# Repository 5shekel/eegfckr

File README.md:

# eegfckr
TLDR>>> brain exciter, a  sencessor to output blinking LEDs in freq between 4-32Hz and tone in a ~30Hz phase

[text is work in progress, not touching audio]
After centuries of using electricity to stimulate and research the brain, optogenetics marks a phase, in which we use light to activate neurons and their pathways. To understand this transformation from electricity to light as a medium for exploring our mind, we will prototype a creative eye-ware with LEDs, which can alter EEG signals in the brain. We will solder a simple circuit that acts as a mind machine device. The final prototype will have a form of a creative eyewear or "eye-ware" mocking some recent history of Google glass mania and other futuristic attempts to hack eyeglasses.

[more pics at imgur](http://imgur.com/a/cNCWE)

# board Layout  
where abusing attiny85 "factory calibrated" 10% error to generate [binaural beats](https://en.wikipedia.org/wiki/Binaural_beats)   

Attiny85 pinout  

## software
in process.   
also see [low.li blog post](http://low.li/story/2011/01/arduino-brain-machine) > [github](https://github.com/LaughterOnWater/Arduino-Brain-Machine)

### tone talk
links on tone lib modfing for the attiny family and some light low level code talk.
[A Tone Generator for Trinket](http://w8bh.net/avr/TrinketTone.pdf)  
[Waveform Generation using an ATtiny85](http://www.technoblogy.com/show?QVN) | [archive.is](https://archive.is/Lsk9m)  
[tinyTune func](http://www.technoblogy.com/show?KVO)   
[programming the LilyPad Arduino: sound](http://web.media.mit.edu/~leah/LilyPad/07_sound.html)  
[link-an-led-with-an-avr](http://www.evilmadscientist.com/2012/blink-an-led-with-an-avr/)  
[http://www.ladyada.net/learn/proj1/blinky.html](http://www.ladyada.net/learn/proj1/blinky.html)  
[binaureal beats using the arduino](http://forum.arduino.cc/index.php?topic=41077.0)  
[brainwave-disruptor](http://blog.ponoko.com/2011/08/05/rich-decibels-brainwave-disruptor/) >> [polytones without delay](https://gist.github.com/5shekel/ce690d048fac5872f0ad)

### upload
using arduino uno as isp  
- add ATtiny board to arduino 1.6.5> 
(see http://highlowtech.org/?p=1695)  
--(TLDR) add [this](https://raw.githubusercontent.com/damellis/attiny/ide-1.6.x-boards-manager/package_damellis_attiny_index.json) to your board manager

- upload sketch files>exampels>arduinoISP to your uno  
- then select tools>programmer>"arduino as isp"  
-- select  
-- board>ATtiny 
-- Processor>ATtiny85  
-- Clock>8Mhz (internal)  

### Components
[BOM google sheet](https://docs.google.com/spreadsheets/d/1JA0BjbYkpqYi8BU7iDlsvR_3m2nQNDry2EhpkC5hDX0/edit?ts=5613f817#gid=0) 

### workshops:  
[TAMI hackerspace wiki page](http://telavivmakers.org/index.php?title=Brain )  
[zimmer workshop #1 pics](http://imgur.com/a/cNCWE) [FB event](https://www.facebook.com/events/823769724411378/)  

##links
[The history of the electrical stimulation of the brain](http://www.cerebromente.org.br/n18/history/stimulation_i.htm)  
[Hans Berger: From Psychic Energy to the EEG](http://methodsinbraincomputerinterfaces.wikispaces.com/file/view/BergerBiography.pdf)  
[Hans Berger portrait](http://neuroportraits.eu/portrait/hans-berger)
[History of glasses](http://www.museumofvision.org/exhibitions/?key=44&subkey=4&relkey=35)  
[1750 Martins Margins type spectacles](http://www.museumofvision.org/collection/artifacts/?accession=1999.024.00059) 
[Guide to Assist in the Identification of Antique Spectacles](http://www.antiquespectacles.com/guide/guide_to_assist.htm)  
Weird eye-ware designs [#1](https://www.flickr.com/photos/x-ray_delta_one/4747873754/) [#2](https://www.flickr.com/photos/x-ray_delta_one/4265173624/in/album-72157622288782911/)  
[E-waste recycled glasses](https://www.facebook.com/ajplusenglish/videos/586570601484451/?pnref=story)  
[chris-marker La Jetée](http://www.theguardian.com/film/2014/apr/15/thrilling-prophetic-chris-marker-experimental-films)  

[headphones that get you high](http://www.sciencealert.com/headphones-that-get-you-high-are-tipped-to-go-on-sale-next-month)  

#text

DIY MIND MACHINES & CREATIVE "EYE-WARE"

"... and you realized that reality is neurology, and is not absolute."
Cronenberg, David. Consumed: A Novel (p. 225)

Subtle change from electricity to light marks a major breakthrough in brain research methodology, which remains to be translated into designing future brain interfaces. After centuries of using electricity to stimulate and research the brain, optogenetics marks a phase, in which we are starting to use light to activate not only brain regions, but actual neurons and their pathways. To understand this transformation from electricity to light as a medium for exploring our mind, we will prototype a creative eye-ware with LEDs, which can alter EEG signals in the brain. We will solder a simple circuit for output blinking LEDs in frequency between 4-32Hz, which serve as basic components to design a mind machine device. The final prototype will have a form of a creative eyewear or "eye-ware" mocking some recent history of Google glass mania and other futuristic attempts to hack eyeglasses. The simple analogue circuit operating a specially positioned LEDs works with the phenomenon of photosensitivity, which can alter the EEG signals. By flashing at certain frequencies and coupled with binaural tones over headphones it can even improve conditions, such as ADHD or trigger various altered states of the mind. Supposedly, such device can even  affect the growth of the individual dendrites on a neuronal level and influence various cognitive functions. With this prototype of a creative eye-ware we plan to look closer into the media archeology behind mind altering devices and various experiments with "biological (animal) electricity" (Luigi Galvani) and "psychic energy" (Hans Berger), but also probe the emergent field of optogenetics and its genetically modified organic "photoswitches". The original experiments with electricity led to the discovery of electroencephalography (EEG) in 1929, but also positron emission tomography (PET) and function magnetic resonance imaging (fMRI), and subsequent attempts to differentiate between metabolic, neural and cognitive processes (glucose concentration, cerebral blood flow, neural activity, mental phenomena, or alpha and beta etc. waves). The present experiments with photons in the case of optogenetics have yet to be discovered applications, metaphors and (nootropic) "neuro-politics", which we want to explore. We will bridge philosophy, brain science and design to create scenarios of future optogenetics with the use of prototypes and mockups. We will try to imagine a future, in which control and alteration of behaviour and mood can happen through light in real time on the level of individual neurons. Would such future bring a total control or unimaginable anarchy? How would devices using optogenetics look like? Will they finally kill the sophists and the delicate art of persuasion, which Plato hated so much, or open infinite space for infinite deception and lying or maybe trigger "sensitivity to  aberrant realities" as the audio-device described by David Cronenberg in his last novel "Consumed"? How to imagine and design for such direct control of our judgement, taste, behaviour through the brain rather than language and experience? Are we facing similar future to the one hinted in a forgotten 1972 David Cronenberg's movie "Secret Weapons" on a drug that enhances fighting skills? We will use his recent novel "Consumed" with its bizarre story of insects, North Korea film industry, obsession with proteins, philosophy of consumerism, and one brilliant idea of filtered hearing aids that can derange human perception and lead to madness as one of the starting points.   Will the future mind machines resemble Cronenberg's organic machinery, such as these madness inducing audiotech devices exploring radical decadence of the senses forgotten by all tech revolutions? Our design will be dark and sinister and use his weird metabolic theme of eating and becoming food, being a consumer and consumed, exotic toys and diseases as means of intercultural exchanges, autonomy and parasitism, against the clear, moralist or other world saving agenda, which lead to very boring designs. Quotes for inspiration:
"When I first got my hearing aids, which were primarily tuned to augment those higher frequencies which are usually the first to disappear with age, it is true that the world instantly became louder and more harsh; it was difficult for someone whose aural landscape had so gradually become more and more muted and dulled to believe that this was hearing as experienced by most people, that this harshness was just the restoration of higher sound frequencies that had been lost. But the most disorienting aspect of this new soundscape was that sounds now carried too much emotion, too much meaning, so that a single sneeze was an expression of rage, the closing of a bedroom door was a pointed separation that would need healing, the smacking of a pillow to reshape it in the middle of the night was an explosive assault that caused my heart to pound with reflexive anger. A recalibration of my reaction to the intensity of sounds was urgently demanded, and though was constantly recalibrating, those unexpected shots of adrenaline still persisted and confused me. I wanted to jerk out of bed and slam the bedroom door and go for a petulant walk in the wet, dark streets, muttering to myself about spousal insult and betrayal. But I recalibrated.
Cronenberg, David (2014-09-30). Consumed: A Novel (p. 217). Scribner. Kindle Edition.

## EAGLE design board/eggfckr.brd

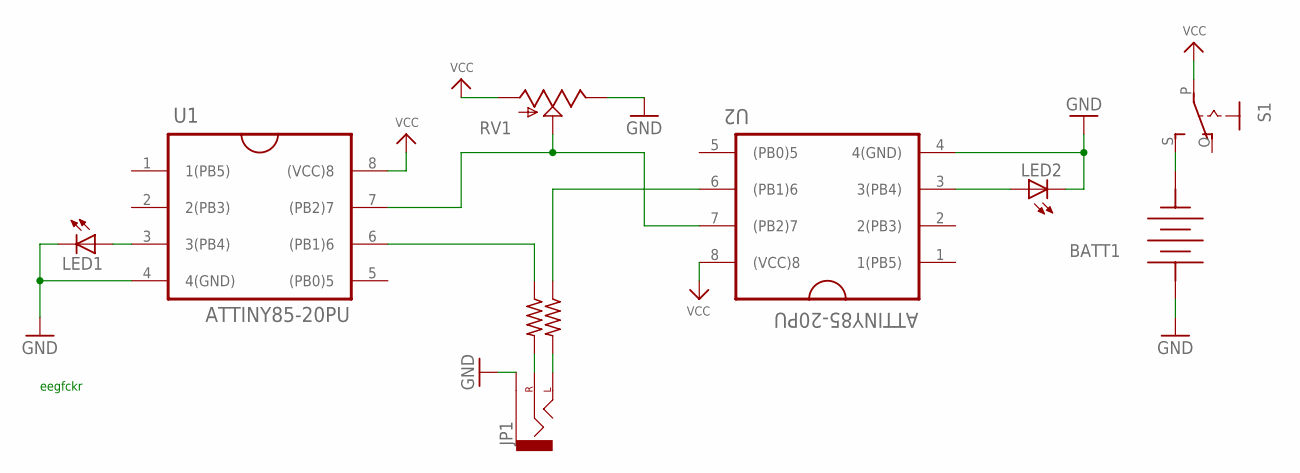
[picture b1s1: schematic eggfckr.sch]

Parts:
BATT1: FKIT-COIN_CELLLIR2450-H; FKIT-LIR2450-H
JP1: AUDIO-JACKSPECIAL_POGO_PINS; STEREOJACK2.5MM_SPECIA_POGOPINS
LED1, LED2: LED3MM
R1, R2: R-US_0204/7; 0204/7
RV1: POT-RV16AF-20; POT_ALPHA_RV16AF-20
S1: EG1218S; EG1218
U1, U2: ATTINY85-20PU; DIP254P762X533-8

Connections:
GND: BATT1.POS, JP1.RING1 (SLEEVE), LED1.K (C), LED2.K (C), RV1.3 (E), U1.4 (4(GND)), U2.4 (4(GND))
unnamed: R1.1, U1.6 ((PB1)6)
unnamed: LED1.A, U1.3 (3(PB4))
unnamed: JP1.TIP (RIGHT), R1.2
unnamed: RV1.2 (S), U1.7 ((PB2)7), U2.7 ((PB2)7)
unnamed: R2.1, U2.6 ((PB1)6)
unnamed: LED2.A, U2.3 (3(PB4))
unnamed: JP1.SHIELD (LEFT), R2.2
unnamed: BATT1.NEG, S1.S
VCC: RV1.1 (A), S1.P, U1.8 ((VCC)8), U2.8 ((VCC)8)

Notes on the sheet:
eegfckr

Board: 2 copper layers, 10 parts (0 on the bottom side), 10 nets, no tracks yet.

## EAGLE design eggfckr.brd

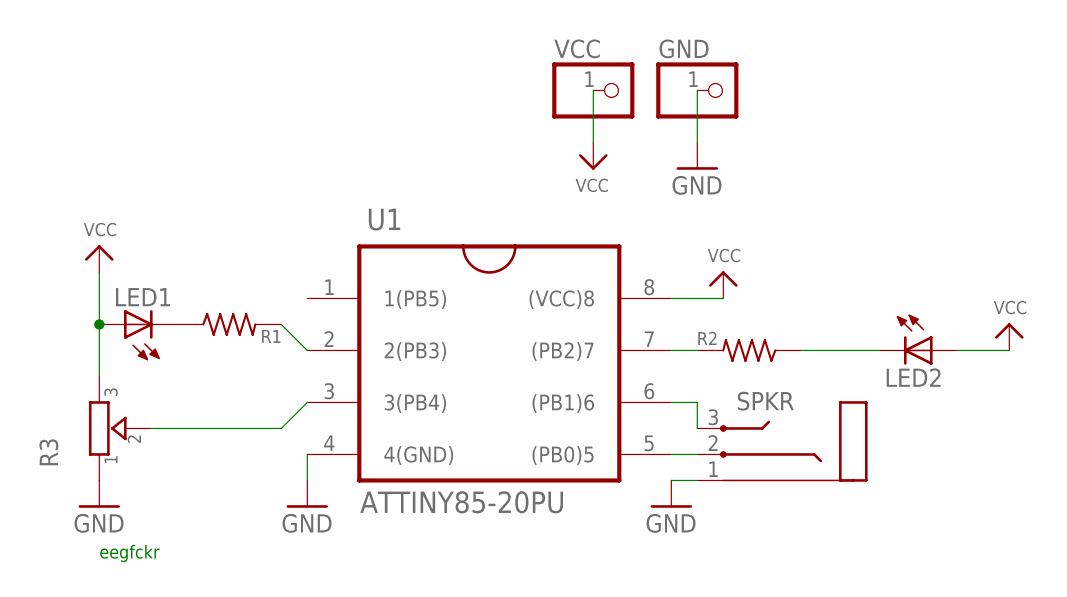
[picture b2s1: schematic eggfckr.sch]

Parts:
GND: HEADER-1X1; 1X01_OVAL
LED1, LED2: LED3MM
R1, R2: R-US_0207/7; 0207/7
R3: TRIMMER-3306F; TRIMMER_3306F
SPKR: AUDIO_STEREOJACK; STX3100
U1: ATTINY85-20PU; DIP254P762X533-8
VCC: HEADER-1X1; 1X01_OVAL

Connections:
GND: GND.1, R3.1, SPKR.1, U1.4 (4(GND))
unnamed: R2.2, U1.7 ((PB2)7)
unnamed: R3.2, U1.3 (3(PB4))
unnamed: SPKR.3, U1.6 ((PB1)6)
unnamed: R1.2, U1.2 (2(PB3))
unnamed: SPKR.2, U1.5 ((PB0)5)
unnamed: LED1.K (C), R1.1
unnamed: LED2.K (C), R2.1
VCC: LED1.A, LED2.A, R3.3, U1.8 ((VCC)8), VCC.1

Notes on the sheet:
eegfckr

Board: 2 copper layers, 9 parts (0 on the bottom side), 9 nets, no tracks yet.

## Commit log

2015-07-11 eagle files for schema
2015-07-21 attiny85 version
2015-07-21 Update README.md
    changed circuit to ATTINY85 kind
2015-08-03 updated readme with prog instcutions
2015-08-03 first blink
2015-08-03 new layout/schema
2015-08-04 failed linear to log pot convertion
2015-08-04 added SVG (print to pdf in eagle, massage with inkscape)
2015-08-04 silluate circuit
2015-08-10 added visuals
2015-08-10 add visuals folder
2015-11-02 added tone to speaker on PB0
2015-11-02 add lib with costum audio jack
2015-11-03 added topor and trying extra channel on attiny
2016-02-17 moved board to board
2016-02-18 added ATTINY85_Tone_Freq_and_Note, from https://github.com/Comingle/ArduinoUtilityPrograms
2016-02-19 added some code from the web, see readme
2016-02-22 added links
2016-02-27 updates for board
2016-02-27 fritzing
2016-02-28 flipped LEDon pin2
2016-02-28 updated frizzting
2016-02-28 rewire VCC/GND
2016-02-28 rewire VCC/GND 2
2016-02-28 working ard attiny85 non sound code
2016-02-28 removed resistor :0
2016-02-28 A4 worksheet
2016-02-28 a bit up
2016-02-28 A BIT MORE
2016-02-28 abit more
2016-05-11 added pinout
2017-04-08 changed routing
2017-04-08 moved fritzing worksheet to visuals
2017-04-08 added btn WIP
2017-04-08 revert ino to pot version
2017-04-10 fixed error in code and handout...
2017-04-11 code
2017-04-13 whats going on'
2017-05-20 new code for dual eyes
2017-05-20 dual
2017-05-20 del tap
2017-05-21 flipped attiny85
2017-05-21 library and split processors
2017-05-24 tone worshop
2017-06-26 workshop, but the leds dont play nice
2018-01-18 add lock files
2018-10-31 getting ready for svg2snhn
2019-05-29 svg beginings

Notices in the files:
parts and their libraries:
SparkFun-Connectors: Licensing: Creative Commons ShareAlike 4.0 International - https://creativecommons.org/licenses/by-sa/4.0
eggfckr: Shamelessly taken from the Adafruit Eagle library (public domain) ... thanks!
